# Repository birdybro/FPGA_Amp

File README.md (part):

# FPGA Amp

FPGA Amp is a physically informed vacuum-tube audio simulator. The immediate
target is a moving-magnet cartridge feeding the two triodes of a 12AX7 through
the passive RIAA network published by Kevin Kennedy in 1998. It is modeled as a
coupled electrical circuit—not as an EQ block followed by a waveshaper.

```text
AT-VM95E R/L source -> 47.5 kΩ || 150 pF -> 12AX7 #1
 -> 47 nF / 210 kΩ / 33.2 kΩ / 10 nF / 3.3 nF passive RIAA
 -> 12AX7 #2 -> 470 nF -> 2.21 MΩ line load
```

The project keeps three categories separate:

- **Reference:** the frozen 1998 circuit, including its measured low-frequency
  RIAA departure.
- **Approximation:** tube-model, integration, LUT, fixed-point, solver, and RTL
  errors measured against the immediately upstream reference.
- **Enhancement:** future subsonic filtering, tube variation, noise, and other
  modern/creative controls, all explicitly opt-in.

## Current measured milestone

The mono reference and complete 768 kHz circuit solver are operating:

- ngspice DC: stage 1 is 180.0 V / 0.992 mA and stage 2 is 192.8 V /
  1.072 mA at a 300 V supply.
- SPICE circuit gain is 41.087 dB at 1 kHz. Relative RIAA error is
  -0.919 to +0.000 dB from 20 Hz to 20 kHz; this is a property of the frozen
  historical network, not digitally corrected.
- The 768 kHz backward-Euler nonlinear nodal model differs from the ngspice
  5 mV-peak, 1 kHz result by -53.10 dB normalized residual and 0.0018 dB RMS
  gain, with no failed solves.
- A four-frequency SPICE transient sweep exposes backward-Euler's audio-band
  phase cost: at 100 Hz it is +0.00131 dB / +0.0244°, while at 20 kHz it is
  -0.0646 dB / +4.72°. Raising backward-Euler to 3.072 MHz still leaves 1.24°
  at 20 kHz. An explicit 768 kHz trapezoidal candidate improves 10/20 kHz
  floating error to at most 0.00846 dB / 0.0582°.
- A separately labeled 384 kHz/8× trapezoidal architecture candidate measures
  at most 0.06653 dB / 0.02234° against the same 10/20 kHz SPICE captures. At
  20 kHz, its complete-circuit selected 4/8/12/16 kHz products remain within
  0.52 dB of 768 kHz for 5 mV, 20 mV, and steady 0.5 V inputs, while a hot
  static-tube stress is 11.33 dB worse but still -118.65 dBc. Distinct
  fixed-point assets now match 1,024 all-bank chord, 1,024 KCL, and 512
  persistent full-solver RTL vectors exactly at 384 kHz with zero solver
  diagnostics. The 127-clock core
  leaves 129 of 256 clocks free at 98.304 MHz. Its Q17.1 chord inverse requires
  signed 19-bit coefficients rather than the 768 kHz core's 18 bits; controlled
  Yosys synthesis measures 13,713 LC / 183 DSP / 10 RAMB18 equivalents versus
  13,158 LC / 174 DSP / 10 RAMB18 equivalents at 768 kHz. The complete
  candidate stream now matches 64 external outputs across 512 nonlinear
  updates exactly, with zero converter, solver, or deadline diagnostics.
  After serializing each decimator center tap and replacing both resamplers'
  reset-cleared shift histories with reset-masked circular distributed memory,
  controlled full-stream synthesis measures 15,716 LC / 8,547 FF / 207 DSP /
  10 RAMB18 equivalents at 384 kHz versus 16,062 / 9,033 / 206 / 10 for 768 kHz.
  Reference mode remains 16×/768 kHz. A 772,608-update paired fixed-stream
  campaign finds
  8× recovery only 0.1875 ms later, with -84.71 dB aligned waveform and
  -81.02 dB audio-band residuals. Known-delay, windowed-sinc alignment measures
  the synthetic pop at -35.92 dB overall, 2.623 mV peak error, and -53.33 dB
  in-band. A layer decomposition measures the identity converters at -67.49 dB
  in-band, floating Newton at -55.71 dB, and fixed at -53.33 dB; same-rate
  fixed/float nulls remain about -59 dB. This supersedes an invalid earlier
  linear-interpolation result. Direct RTL capture matches the corresponding
  fixed models for all 24,576 pop/recovery outputs and 294,912 nonlinear
  updates at both rates with zero diagnostics. A matched, unfitted absolute
  pop-response comparison against ngspice measures -61.47 dB residual at the
  48 kHz output boundary for 384 kHz and -61.00 dB for 768 kHz; maximum errors
  are 0.539 and 0.546 mV, respectively, with zero failed floating solves. This
  experiment therefore does not support keeping 16× on transient-accuracy
  grounds. The earlier shifting-history three-pin harness packs on XC7A100T at
  63,902 LUTX / 14,737 FFX / 4,071 CARRY4 / 207 DSP, but heap placement does
  not legalize. That baseline legally places on XC7A200T with
  nextpnr's static placer at only 34.40 MHz versus 98.304 MHz. The experimental
  backend's `DEFAULT` grade is not qualified -1 signoff, but the 2.86× miss is
  decisive enough to skip routing. An explicit 49.152 MHz fabric schedule then
  halves every enable interval while preserving the same 384 kHz arithmetic:
  its 127-clock solver fits exactly within the 128-clock internal period, and
  the complete 64-output/512-update regression remains bit-exact with zero
  diagnostics. Baseline static A200T placement improves to 38.34 MHz versus
  49.152 MHz. Circular decimator history then cuts the packed design to 58,363
  LUTX / 10,562 FFX / 4,099 CARRY4 / 207 DSP and makes heap placement legal for
  the first time, but its 22.79 MHz estimate still fails timing. Static
  placement initially reaches 38.38 MHz. Circular interpolation then reduces
  the pack to 56,041 LUTX / 8,589 FFX / 4,116 CARRY4 / 207 DSP and improves
  static placement to 41.27 MHz. The completed legal route reaches 48.482 MHz,
  only 1.38% below 49.152 MHz. Its 20.626 ns critical path starts at solver
  state selection, crosses voltage selection and plate-pin conversion, and
  ends in the factorized-tube input mapping. A separately named exact
  123-clock parallel/pipelined profile instead grows to 242 DSPs and places at
  only 39.62 MHz, so it is rejected. A route-guided tube-pin prefetch plus
  diagnostic-only KCL maximum pipeline also preserves all 64 outputs / 512
  updates and the 127-clock latency. After removing an invalid-only dead
  maximum load it routes legally at 47.07 MHz, but its 21.24 ns chord-preview
  path is slower than the baseline and is likewise not promoted. The route
  remains diagnostic rather than timing closure or a bitstream claim. A
  zero-latency late-selector candidate instead converts current and corrected
  stage-one tube pins independently and selects only the two 32-bit pin buses.
  It remains bit-exact at 127 clocks, synthesizes to 15,645 LC / 8,589 FF /
  207 DSP / 10 RAMB18 equivalents, and routes legally at 48.700 MHz in seed 1.
  That is the best measured route but still misses 49.152 MHz by 0.92%; seed 2
  reaches only 45.051 MHz. Combining it with the register-heavy four-boundary
  maximum sideband was stopped after a pathological first routing iteration
  and is not promoted. A lower-state serial maximum instead scans the nine
  stable residual rows during terminal chord work. It matches 2,048 KCL
  vectors and the complete stream exactly, reduces the pack to 54,699 LUTX /
  8,657 FFX / 4,044 CARRY4 / 207 DSP, and routes legally in 14 iterations, but
  reaches only 47.567 MHz through the now-exposed chord-to-tube path.
  Registering the six raw tube nodes on the exact one-cycle-early chord preview
  removes that path without adding a solver clock: the same complete stream is
  bit-exact at 127 clocks, Yosys measures 15,220 LC / 8,855 FF / 207 DSP /
  10 RAMB18 equivalents, and a legal seed-1 A200T route reaches 61.072 MHz
  against 49.152 MHz. The 16.37 ns critical path is now terminal-current/state
  arithmetic, with 6.44 ns logic and 9.94 ns routing. This closes the target
  under nextpnr's experimental `DEFAULT` grade. Seed 2 independently routes at
  51.080 MHz with 0.77 ns positive estimated slack and a different 19.58 ns
  registered-node-to-tube critical path. Neither result is qualified -1
  signoff or physical validation. The selected seed-1 FASM now also passes a
  wholly open Project-X-Ray bitstream stage: 20,230 frame records become a
  reproducible 9,730,907-byte `.bit`, and `bitread -C` validates 24,060
  configuration frames / 2,432,650 words. Two conversions have identical
  SHA-256 `98a53adf...2b9dcb`; the script fixes only header timestamp metadata
  and records that hardware remains unprogrammed/unvalidated. The 8×
  architecture remains an explicit candidate and reference mode remains 16×.
  The selected 8× profile now also runs through the actual calibrated fabric
  adapter, asynchronous I²S bridge, register bank, and SPI transport. Exact
  regressions cover 64 adapter frames, 64 serial inputs / 44 observable DAC
  frames, control transitions, and 15 SPI frames. Yosys measures 15,699 LC /
  9,085 FF for the adapter and 16,614 LC / 11,586 FF for the full SPI/I²S top;
  both use 217 DSPs / 10 RAMB18 equivalents with zero structural problems.
  The Nexys Video clock leaf now cascades two checked XC7 MMCMs from its real
  100 MHz oscillator to exact 12.288 MHz codec MCLK and 49.152 MHz fabric
  clocks. Its clock-only open route and CRC-readable bitstream pass. A tested
  /16 divider now produces 3.072 MHz BCLK with owning-domain reset release;
  a bus-level-tested open-drain I2C writer and 27-register ADAU1761 startup
  sequence pass exact-byte and fail-stop NACK simulation. The codec layer is
  warning-free in XC7 synthesis at 88 estimated logic cells / 94 flip-flops /
  no DSP or BRAM. The codec remains subordinate to FPGA-provided BCLK/LRCLK,
  and line unmute occurs last. The actual Nexys Video wrapper now composes that
  clock/reset/bootstrap path with one shared codec LRCLK, the 384 kHz
  timing-closed phono profile, SPI control, open-drain I2C, and fail-closed DAC
  data. A mutation-tested contract checks all 18 LOC/IOSTANDARD pairs, active-
  low reset, internal 3.072 MHz BCLK constraint, model rate, and startup mute;
  a separate guard regression proves that serial DAC data stays zero and the
  I2S bridge/FIFO serial ports stay reset through two BCLK synchronizer edges
  after configuration. This prevents undefined ADC frames during the 10 ms
  bootstrap from pre-filling the receive FIFO. Complete synthesis reports
  16,688 estimated logic cells / 11,687 flip-flops / 217 DSPs / ten RAMB18
  equivalents and zero structural problems. Programming, physical ACKs,
  analog audio, and clock measurements remain open. The full open A200T route
  converges legally in 20 iterations and estimates 54.663 MHz against the
  49.152 MHz fabric constraint and 123.457 MHz against 3.072 MHz BCLK. The
  pinned Project-X-Ray stage twice emits the same CRC-readable 9,730,825-byte
  bitstream at SHA-256 `5f196e52...b09dbb8`. This closes the experimental open
  implementation gate only; the `DEFAULT` timing grade is not qualified -1
  signoff and the image has not been programmed. A non-programming hardware
  preflight now rechecks that exact artifact's part, length, SHA-256, and saved
  `bitread -C` evidence before asking openFPGALoader to detect the official
  `nexysVideo` board profile. The current host has neither openFPGALoader nor a
  Nexys Video USB device, so physical bring-up is explicitly blocked rather
  than inferred from the image.
- A 100 ms floating overload comparison finds the trapezoidal candidate finite
  and convergent through 1.5 V peak / 26.4 µA stage-two grid current. At 20 mV,
  its 10% / 1% / 1 mV recovery agrees with backward Euler within 2.6 µs. Both
  retain the modeled long recovery above 0.5 V; trapezoidal does not conceal or
  correct that reference behavior.
- The bit-accurate trapezoidal candidate uses the wide Q28/Q32 node contract,
  Q30 previous capacitor voltage, and explicit signed Q4.44 previous capacitor
  current. Across six 5 mV points from 20 Hz through 20 kHz it stays within
  0.000131 dB / 0.000784° of floating trapezoidal, with zero convergence,
  saturation, range, or correction-fallback events. Its RTL is bit-exact at the
  same 116-clock schedule, including the banked large-signal captures below.
  It remains an optional numerical candidate rather than a silent reference
  change.
- In the 5 ms burst gate, fixed trapezoidal stays diagnostic-clean through
  0.5 V peak and retains the same severe-overload boundary as backward Euler:
  1.0/1.5 V cause 1,107/1,690 residual failures and 1.5 V causes 4,048 tube-
  domain clips. Stored capacitor current reaches 203.34 uA with no arithmetic
  saturation. The doubled 470 nF companion coefficient requires signed 48-bit
  Q0.47, one bit wider than the current backward-Euler RTL KCL contract.
- The 128 × 256 Q0.31 tube LUT has 0.139 µA mean and 9.33 µA worst absolute
  error in a 100,000-point full-range probe.
- The complete bit-accurate three-pass chord candidate is -57.87 dB normalized
  residual from analytical/full-Newton float on the initial multitone; isolated
  state/chord error is -70.33 dB relative to the same circuit using the tube LUT.
- A settled 1 kHz sweep exposes a narrower low-level limitation: at 5 mV peak,
  fixed THD is 0.0733% versus 0.0191% analytical. Doubling either LUT axis does
  not fix the existing 2-D implementation.
- A new factorized Koren candidate replaces that current surface with three
  value/slope 1-D tables and cubic Hermite interpolation. Its bit-accurate Python
  model measures 50.6 nA worst plate-current error in 100,000 points and 0.0188%
  THD at 5 mV versus 0.0191% analytical. Its 1,024-point grid-current branch
  measures 12.55 nA worst / 2.82 nA active-region RMS error; total raw storage
  is 262,144 bits (14.22 raw RAMB18 equivalents). Standalone RTL is exact across
  4,110 vectors at the existing eight-clock latency; structural synthesis
  reports 1,496 logic cells, 35 DSP48E1s, and 8 RAMB18E1 + 1 RAMB36E1. Solver and
  complete-stream modes are also
  bit-exact at the unchanged 126-clock solver schedule.
- A separately named value-only factorized candidate keeps the physical Koren
  factorization and eight-clock interface while using 1,024/8,192/4,096 linear
  tables. Its dense fixed probe measures 47.49 nA worst plate-current error;
  tube, wide-solver, and complete 127-clock terminal-solver RTL are bit-exact.
  The isolated tube routes at 113.24 MHz with 27 DSPs. Full solver synthesis
  uses 166 DSPs and 13 RAMB18E1 + 5 RAMB36E1; routing is still in progress, so
  this remains an FPGA approximation candidate rather than reference mode.
- The SystemVerilog tube lookup accepts physical Q-format voltages, is
  bit-exact for 4,096 randomized vectors, and has eight-clock latency.
- The nine-node chord corrector is bit-exact for 1,024 randomized/boundary
  vectors, including 18 saturation cases, with ten-clock latency; XC7 synthesis
  uses 9 DSP48E1 blocks and no block RAM.
- A device-neutral depth-8 dual-clock FIFO now crosses full audio words with
  binary local/Gray synchronized pointers, two-flop CDC synchronizers, registered
  reads, sticky overflow/underflow, and conservative local-domain occupancy plus
  high-water diagnostics. Unrelated 100/71.4 MHz test clocks preserve a 128-word
  wrap sequence after directed full/empty faults; directed fill reaches exactly
  depth eight and both estimates return to zero after drain. Generic XC7 synthesis
  uses 127 logic cells / 331 flip-flops / no DSP or RAM; Yosys intentionally
  expands this small 8×32 memory to registers. Embedded formal invariants exist,
  and a depth-four formal instance now passes 13 properties for all arbitrary
  clock/control interleavings over 32 global steps. A separate trace reaches
  full plus both fault stickies. This is bounded safety evidence, not unbounded
  induction or a physical metastability claim.
- Separate I²S receive/transmit blocks now implement signed 24-bit stereo in
  32-BCLK slots with the mandatory one-clock I²S delay. A warning-free 16-frame
  loopback covers positive/negative endpoints, independent 32-period slot/delay
  monitoring, injected LRCLK framing failure, and transmit underflow/clear.
  Warning-free XC7 synthesis measures 35 LC / 105 rising-edge flops for receive
  and 97 LC / 137 falling-edge flops for transmit, with no DSP or RAM.
- A bidirectional I²S asynchronous bridge now composes those protocol blocks
  with independent depth-8 stereo-frame FIFOs. A warning-free test sends 20
  exact frames from BCLK to an unrelated fabric clock and back while applying
  fabric receive backpressure; all six bridge diagnostics remain clean apart
  from deliberate DAC startup starvation, which clears in its owning domain.
  Directed multi-frame receive backpressure records 3/3-frame receive and
  4/4-frame transmit high-water marks without loss. Flattened XC7
  synthesis reports 571 LC / 1,547 FF / no DSP or RAM. The small
  8×64 memories are explicitly register-expanded.
- A Gray-counter audio-clock monitor now measures BCLK over 32,768 fabric
  clocks, accepts 1,024 ± 1 edges, and requires three consecutive windows for
  lock. Warning-free directed RTL acquires at the exact ratio, observes 11
  rather than 10 edges after a deliberate speed change, drops lock/latches the
  error, reacquires, clears, detects a stopped clock as zero edges, and revokes
  live state on BCLK reset. Sixteen properties hold over 32-step arbitrary-clock
  traces in a reduced instance, and a witness locks before retaining a bad-rate
  error. The pin top measures exactly 1,024 edges in four windows. Standalone
  synthesis is 68 LC / 125 FF / no DSP or RAM. This detects gross rate error;
  FIFO drift remains the longer-term mismatch diagnostic and neither mechanism
  performs rate matching.
  The register-controlled wrapper now treats missing lock or retained rate
  error as an explicitly modern immediate-mute condition. A shortened-window
  integration test proves startup qualification, stopped-BCLK clamp, recovery
  that remains latched, coherent fault snapshot, and host clear before release;
  model scheduling continues silently so the receive FIFO is not filled.
- A reusable 16-bit held-bus CDC snapshot now uses a four-phase handshake, two
  data synchronizer stages, and a final settling clock. Three warning-free
  captures survive unrelated clocks and a destination reset during a request;
  nine properties also hold for every 40-step arbitrary-clock formal
  interleaving after shared startup reset, with a nonzero complete-transfer
  witness. Generic synthesis is 5 LC / 75 FF with no warnings. The register
  bank waits for this capture before advancing its snapshot sequence and packs
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
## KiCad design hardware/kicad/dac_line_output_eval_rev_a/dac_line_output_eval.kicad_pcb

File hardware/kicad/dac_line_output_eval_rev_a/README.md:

# PCM5242 DAC / protected line-output Rev-A EVT board

This directory contains a routed four-layer KiCad 10 evaluation board for the
stereo FPGA-to-line-output path. It is a concrete bench prototype, not a
production fabrication release and not evidence of measured audio performance.
Open `dac_line_output_eval.kicad_pro` in KiCad 10. KiCad does not live-reload
files changed by the generator, so close/reopen the board after regeneration.

```text
FPGA 24-bit I2S + 24.576 MHz SCK
  -> PCM5242 in external-clock slave / I2C mode
  +-> 499 ohm/leg + 1 nF differential reconstruction -> fail-open relays -> balanced harness
  +-> 499 ohm + 2.2 nF shunt reconstruction -> fail-open relay -> isolated-RCA harness
```

The board is 112 x 72 mm with F.Cu / continuous L2 GND / L3 POWER_SIG /
B.Cu. Digital/control entry, DAC and charge pump, reconstruction networks,
relays, and panel harnesses are physically partitioned. The harness connectors
are EVT choices; production XLR/RCA mechanics belong to the enclosure design.

## Fixed electrical contract

- DAC: PCM5242RHBR, 48 kHz slave, 24-bit I2S in 32-BCK channel slots.
- Clocks: 24.576 MHz external SCK (`512 fS`), 3.072 MHz BCK (`64 fS`), and
  48 kHz LRCK. External SCK is used instead of making the DAC PLL the reference.
- Control: I2C mode with `MODE1=0`, `MODE2=1`, `ADR1=0`, and `ADR2=0`.
  Reference firmware must hold XSMT low while configuring and reading back a
  unity path; optional miniDSP/creative processing is disabled in reference
  mode.
- Supplies: separate external 3.7 V analog and digital feeds post-regulated by
  two TPS7A2033 devices, plus a separate 5 V relay feed. The power board owns
  sequencing and the single reviewed chassis/signal-ground bond.
- Balanced output: the official EVM-style 499 ohm per-leg and 1 nF
  differential network. Into 20 kilohm differential, calculated full scale is
  4.00038 V RMS at DC and 3.97214 V RMS at 20 kHz.
- RCA output: the data-sheet-style 499 ohm / 2.2 nF single-ended network. Into
  10 kilohm, calculated full scale is 2.00019 V RMS at DC and 1.98314 V RMS at
  20 kHz.
- Output switching: three Omron G6K-2F-Y 5 V relays use only normally-open
  contacts, so loss of power opens every signal output.

Two SN74LVC1G08 gates provide independent fail-low interlocks:

```text
LINE_RELAY_EN_SAFE = LINE_RELAY_EN_CTL AND HARD_MUTE_N
DAC_XSMT_SAFE      = DAC_SOFT_UNMUTE_CTL AND HARD_MUTE_N
```

Each input is pulled low. The external supervisor can therefore force both
PCM5242 soft mute and physical relay mute even if the controller is stuck high,
reset, absent, or unpowered. The intended unmute order is configure/read back
the DAC while XSMT is low, energize output relays, then raise XSMT. Mute reverses
that order after allowing the DAC ramp to finish.

`design.py` is the auditable source for exact clock, loading, output-level, and
reconstruction-response calculations. Its committed result is
`design_calculations.json`.

## Reproduction and verification

From the repository root:

```sh
make kicad-dac-line-check
make kicad-dac-line-render
```

To regenerate and route from source, set `FREEROUTING_JAR` to Freerouting 2.2.4
or a verified compatible release:

```sh
make kicad-dac-line-route FREEROUTING_JAR=/path/to/freerouting.jar
make kicad-dac-line-check
```

The route script rotates the PCM5242 so its clock pins face the digital side and
its four analog outputs face the reconstruction networks. Freerouting completes
the dense routing; a deterministic reviewed back-edge trace finishes J2.4 I2C
SDA without passing through the header's other even-numbered pads.

The committed board passes KiCad ERC and DRC with zero violations and zero
unconnected items. `verify.py` also locks the PCM5242 and interlock pad maps,
mode straps, normally-open relay contacts, filter values, DNP chassis options,
calculation consistency, board stack/outline, and minimum routing geometry.

The matching open RTL now includes the 20-write configuration bootstrap,
24-operation page-aware readback verifier, and periodic clock/error/short/power
monitor. The integrated controller requires a 48-transaction success path
before `unmute_permitted` and revokes it on a later fault. A separate
`dac_line_output_sequencer` maps that permission to the actual board pins:
`LINE_RELAY_EN_CTL` rises first, `DAC_SOFT_UNMUTE_CTL` follows after a default
5 ms, and orderly mute reverses the order. Emergency mute drops both registered
permissions on the next fabric edge; `HARD_MUTE_N` remains the independent
asynchronous hardware veto. All bus/sequence tests and Yosys structural checks
pass, but no populated-board timing or audio behavior is claimed.

## Release gates

Do not order this as a production board until all of the following are closed:

- PCM5242 control is integrated onto the selected FPGA pins and every physical
  mute transition is verified with the external supervisor able to dominate a
  stuck controller;
- loaded THD+N, dynamic range, frequency response, channel balance, crosstalk,
  output impedance, DC, and clipping are measured on populated hardware;
- power-up, shutdown, brownout, missing-clock, hot-plug, and harness-unplug
  behavior are measured without an audible or damaging transient;
- enclosure-qualified XLR/RCA connectors, pin-1/chassis treatment, isolated
  RCA mounting, and keyed harnesses are selected;
- the provisional PESD5V0X1BCL output clamps pass leakage/capacitance/audio and
  IEC ESD/EFT/RF-immunity qualification; and
- a fabricator stackup, DFM, return-current, thermal, assembly, and sourcing
  review is complete.

## Primary component sources

- [TI PCM5242 data sheet](https://www.ti.com/lit/ds/symlink/pcm5242.pdf)
- [TI PCM5242EVM user guide](https://www.ti.com/lit/ug/slau592a/slau592a.pdf)
- [TI TPS7A20 data sheet](https://www.ti.com/lit/ds/symlink/tps7a20.pdf)
- [TI SN74LVC1G08 data sheet](https://www.ti.com/lit/ds/symlink/sn74lvc1g08.pdf)
- [Omron G6K relay family](https://components.omron.com/sg-en/products/relays/G6K)

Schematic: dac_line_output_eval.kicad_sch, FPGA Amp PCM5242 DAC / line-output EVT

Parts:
C1: 10nF_X7R; C_0603_1608Metric
C2: 100nF_X7R_LDOO; C_0402_1005Metric
C3: 2.2uF_X7R_FLY; C_0603_1608Metric
C4: 2.2uF_X7R_VNEG; C_0603_1608Metric
C5: 100nF_X7R_AVDD; C_0402_1005Metric
C6: 10uF_X5R_AVDD; C_0805_2012Metric
C7: 100nF_X7R_CPVDD; C_0402_1005Metric
C8: 2.2uF_X7R_CPVDD; C_0603_1608Metric
C9: 100nF_X7R_DVDD; C_0402_1005Metric
C10: 10uF_X5R_DVDD; C_0805_2012Metric
C11, C12: 100nF_X7R; C_0402_1005Metric
C20, C21: 1nF_C0G_DIFF; C_0603_1608Metric
C22, C23: 2.2nF_C0G_SE; C_0603_1608Metric
C30, C33: 1uF_X7R_LDO_IN; C_0805_2012Metric
C31, C34: 2.2uF_X7R_LDO_OUT; C_0805_2012Metric
C32: 10uF_X5R_ANALOG_BULK; C_0805_2012Metric
C35: 10uF_X5R_DIGITAL_BULK; C_0805_2012Metric
C36: 10uF_X5R_RELAY_BULK; C_0805_2012Metric
C50: DNP_4.7nF_CHASSIS; C_1206_3216Metric
D1, D2, D3: 1N4148W_FLYBACK; D_SOD-123
D4, D5, D6, D7, D8, D9: PESD5V0X1BCL_EVT; D_SOD-882
J1: DAC_AUDIO; PinHeader_2x05_P2.54mm_Vertical
J2: DAC_CONTROL; PinHeader_2x05_P2.54mm_Vertical
J3: POWER_INPUT; PinHeader_2x04_P2.54mm_Vertical
J4: BALANCED_PANEL_HARNESS_EVT; JST_XH_B8B-XH-A_1x08_P2.50mm_Vertical
J5: RCA_PANEL_HARNESS_EVT; JST_XH_B3B-XH-A_1x03_P2.50mm_Vertical
K1: G6K-2F-Y-5V_FAIL_OPEN_1; Relay_DPDT_Omron_G6K-2F-Y
K2: G6K-2F-Y-5V_FAIL_OPEN_2; Relay_DPDT_Omron_G6K-2F-Y
K3: G6K-2F-Y-5V_FAIL_OPEN_3; Relay_DPDT_Omron_G6K-2F-Y
Q1, Q2, Q3: MMBT3904; SOT-23
R1, R2, R3, R4: 0R_LINK; R_0402_1005Metric
R5: 1k; R_0603_1608Metric
R6, R12, R13, R14: 100k_FAIL_MUTE; R_0603_1608Metric
R7, R8: 4.7k; R_0603_1608Metric
R9, R10: 0R_LINK; R_0603_1608Metric
R11: 10k; R_0603_1608Metric
R20, R21, R22, R23, R24, R25: 499R_0.1%; R_0805_2012Metric
R31, R32, R33: 2.2k; R_0603_1608Metric
R34, R35, R36: 100k; R_0603_1608Metric
R40: 1R_ANALOG_ISOLATION; R_0805_2012Metric
R50: DNP_0R_CHASSIS_BOND; R_1206_3216Metric
TP1: +3V3A; TestPoint_Pad_D1.0mm
TP2: +3V3D; TestPoint_Pad_D1.0mm
TP3: DAC_XSMT_PIN; TestPoint_Pad_D1.0mm
TP4: LINE_RELAY_EN_SAFE; TestPoint_Pad_D1.0mm
TP5: L_RCA_OUT; TestPoint_Pad_D1.0mm
TP6: R_RCA_OUT; TestPoint_Pad_D1.0mm
TP7: CHASSIS; TestPoint_Pad_D1.0mm
TP8: GND; TestPoint_Pad_D1.0mm
U1: PCM5242RHBR; Texas_RHB0032E_VQFN-32-1EP_5x5mm_P0.5mm_EP3.45x3.45mm_Therm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
U2: TPS7A2033PDBVR_ANALOG; SOT-23-5
U3: TPS7A2033PDBVR_DIGITAL; SOT-23-5
U4: SN74LVC1G08DBVR_RELAY_INTERLOCK; SOT-23-5
U5: SN74LVC1G08DBVR_XSMT_INTERLOCK; SOT-23-5

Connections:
+3V3A: C5.1 (+3V3A), C6.1 (+3V3A), C7.1 (+3V3A), C8.1 (+3V3A), C32.1 (+3V3A), R40.2 (+3V3A), TP1.1, U1.5 (+3V3A), U1.14 (+3V3A)
+3V3A_RAW: C31.1 (+3V3A_RAW), R40.1 (+3V3A_RAW), U2.5 (+3V3A_RAW)
+3V3D: C9.1 (+3V3D), C10.1 (+3V3D), C11.1 (+3V3D), C12.1 (+3V3D), C34.1 (+3V3D), C35.1 (+3V3D), J1.9 (+3V3D), J2.1 (+3V3D), R7.1 (+3V3D), R8.1 (+3V3D), TP2.1, U1.4 (+3V3D), U1.24 (+3V3D), U3.5 (+3V3D), U4.5 (+3V3D), U5.5 (+3V3D)
+3V7A_IN: C30.1 (+3V7A_IN), J3.1 (+3V7A_IN), U2.1 (+3V7A_IN), U2.3 (+3V7A_IN)
+3V7D_IN: C33.1 (+3V7D_IN), J3.3 (+3V7D_IN), U3.1 (+3V7D_IN), U3.3 (+3V7D_IN)
+5V_RELAY: C36.1 (+5V_RELAY), D1.1 (+5V_RELAY), D2.1 (+5V_RELAY), D3.1 (+5V_RELAY), J3.5 (+5V_RELAY), K1.1 (+5V_RELAY), K2.1 (+5V_RELAY), K3.1 (+5V_RELAY)
CHASSIS: C50.1 (CHASSIS), D4.1 (CHASSIS), D5.1 (CHASSIS), D6.1 (CHASSIS), D7.1 (CHASSIS), D8.1 (CHASSIS), D9.1 (CHASSIS), J3.7 (CHASSIS), J4.3 (CHASSIS), J4.7 (CHASSIS), R50.1 (CHASSIS), TP7.1
CP_FLY_N: C3.2 (CP_FLY_N), U1.8 (CP_FLY_N)
CP_FLY_P: C3.1 (CP_FLY_P), U1.6 (CP_FLY_P)
DAC_BCK: R2.2 (DAC_BCK), U1.27 (DAC_BCK)
DAC_BCK_IN: J1.3 (DAC_BCK_IN), R2.1 (DAC_BCK_IN)
DAC_DIN: R4.2 (DAC_DIN), U1.28 (DAC_DIN)
DAC_DIN_IN: J1.7 (DAC_DIN_IN), R4.1 (DAC_DIN_IN)
DAC_LDOO: C2.1 (DAC_LDOO), U1.2 (DAC_LDOO)
DAC_LN: R21.1 (DAC_LN), U1.11 (DAC_LN)
DAC_LP: R20.1 (DAC_LP), R24.1 (DAC_LP), U1.10 (DAC_LP)
DAC_LRCK: R3.2 (DAC_LRCK), U1.31 (DAC_LRCK)
DAC_LRCK_IN: J1.5 (DAC_LRCK_IN), R3.1 (DAC_LRCK_IN)
DAC_RN: R23.1 (DAC_RN), U1.12 (DAC_RN)
DAC_RP: R22.1 (DAC_RP), R25.1 (DAC_RP), U1.13 (DAC_RP)
DAC_SCK: R1.2 (DAC_SCK), U1.26 (DAC_SCK)
DAC_SCK_IN: J1.1 (DAC_SCK_IN), R1.1 (DAC_SCK_IN)
DAC_SOFT_UNMUTE_CTL: J2.5 (DAC_SOFT_UNMUTE_CTL), R14.1 (DAC_SOFT_UNMUTE_CTL), U5.1 (DAC_SOFT_UNMUTE_CTL)
DAC_VNEG: C4.1 (DAC_VNEG), U1.9 (DAC_VNEG)
DAC_XSMT_PIN: C1.1 (DAC_XSMT_PIN), R5.2 (DAC_XSMT_PIN), R6.1 (DAC_XSMT_PIN), TP3.1, U1.1 (DAC_XSMT_PIN)
DAC_XSMT_SAFE: R5.1 (DAC_XSMT_SAFE), U5.4 (DAC_XSMT_SAFE)
GND: C1.2 (GND), C2.2 (GND), C4.2 (GND), C5.2 (GND), C6.2 (GND), C7.2 (GND), C8.2 (GND), C9.2 (GND), C10.2 (GND), C11.2 (GND), C12.2 (GND), C22.2 (GND), C23.2 (GND), C30.2 (GND), C31.2 (GND), C32.2 (GND), C33.2 (GND), C34.2 (GND), C35.2 (GND), C36.2 (GND), C50.2 (GND), J1.2 (GND), J1.4 (GND), J1.6 (GND), J1.8 (GND), J1.10 (GND), J2.2 (GND), J2.9 (GND), J2.10 (GND), J3.2 (GND), J3.4 (GND), J3.6 (GND), J3.8 (GND), J4.4 (GND), J4.8 (GND), J5.2 (GND), Q1.2 (GND), Q2.2 (GND), Q3.2 (GND), R6.2 (GND), R11.2 (GND), R12.2 (GND), R13.2 (GND), R14.2 (GND), R34.2 (GND), R35.2 (GND), R36.2 (GND), R50.2 (GND), TP8.1, U1.3 (GND), U1.7 (GND), U1.15 (GND), U1.22 (GND), U1.23 (GND), U1.32 (GND), U1.33 (GND), U2.2 (GND), U3.2 (GND), U4.3 (GND), U5.3 (GND)
HARD_MUTE_N: J2.8 (HARD_MUTE_N), R13.1 (HARD_MUTE_N), U4.2 (HARD_MUTE_N), U5.2 (HARD_MUTE_N)
I2C_SCL: R7.2 (I2C_SCL), R9.2 (I2C_SCL), U1.18 (I2C_SCL)
I2C_SCL_IN: J2.3 (I2C_SCL_IN), R9.1 (I2C_SCL_IN)
I2C_SDA: R8.2 (I2C_SDA), R10.2 (I2C_SDA), U1.17 (I2C_SDA)
I2C_SDA_IN: J2.4 (I2C_SDA_IN), R10.1 (I2C_SDA_IN)
K1_BASE: Q1.1 (K1_BASE), R31.2 (K1_BASE), R34.1 (K1_BASE)
K1_COIL_LOW: D1.2 (K1_COIL_LOW), K1.8 (K1_COIL_LOW), Q1.3 (K1_COIL_LOW)
K2_BASE: Q2.1 (K2_BASE), R32.2 (K2_BASE), R35.1 (K2_BASE)
K2_COIL_LOW: D2.2 (K2_COIL_LOW), K2.8 (K2_COIL_LOW), Q2.3 (K2_COIL_LOW)
K3_BASE: Q3.1 (K3_BASE), R33.2 (K3_BASE), R36.1 (K3_BASE)
K3_COIL_LOW: D3.2 (K3_COIL_LOW), K3.8 (K3_COIL_LOW), Q3.3 (K3_COIL_LOW)
LINE_RELAY_EN_CTL: J2.6 (LINE_RELAY_EN_CTL), R12.1 (LINE_RELAY_EN_CTL), U4.1 (LINE_RELAY_EN_CTL)
LINE_RELAY_EN_SAFE: R31.1 (LINE_RELAY_EN_SAFE), R32.1 (LINE_RELAY_EN_SAFE), R33.1 (LINE_RELAY_EN_SAFE), TP4.1, U4.4 (LINE_RELAY_EN_SAFE)
L_BAL_N_FILT: C20.2 (L_BAL_N_FILT), K1.6 (L_BAL_N_FILT), R21.2 (L_BAL_N_FILT)
L_BAL_N_OUT: D5.2 (L_BAL_N_OUT), J4.2 (L_BAL_N_OUT), K1.5 (L_BAL_N_OUT)
L_BAL_P_FILT: C20.1 (L_BAL_P_FILT), K1.3 (L_BAL_P_FILT), R20.2 (L_BAL_P_FILT)
L_BAL_P_OUT: D4.2 (L_BAL_P_OUT), J4.1 (L_BAL_P_OUT), K1.4 (L_BAL_P_OUT)
L_RCA_FILT: C22.1 (L_RCA_FILT), K3.3 (L_RCA_FILT), R24.2 (L_RCA_FILT)
L_RCA_OUT: D8.2 (L_RCA_OUT), J5.1 (L_RCA_OUT), K3.4 (L_RCA_OUT), TP5.1
OB_PRESENT_N: J2.7 (OB_PRESENT_N), R11.1 (OB_PRESENT_N)
R_BAL_N_FILT: C21.2 (R_BAL_N_FILT), K2.6 (R_BAL_N_FILT), R23.2 (R_BAL_N_FILT)
R_BAL_N_OUT: D7.2 (R_BAL_N_OUT), J4.6 (R_BAL_N_OUT), K2.5 (R_BAL_N_OUT)
R_BAL_P_FILT: C21.1 (R_BAL_P_FILT), K2.3 (R_BAL_P_FILT), R22.2 (R_BAL_P_FILT)
R_BAL_P_OUT: D6.2 (R_BAL_P_OUT), J4.5 (R_BAL_P_OUT), K2.4 (R_BAL_P_OUT)
R_RCA_FILT: C23.1 (R_RCA_FILT), K3.6 (R_RCA_FILT), R25.2 (R_RCA_FILT)
R_RCA_OUT: D9.2 (R_RCA_OUT), J5.3 (R_RCA_OUT), K3.5 (R_RCA_OUT), TP6.1

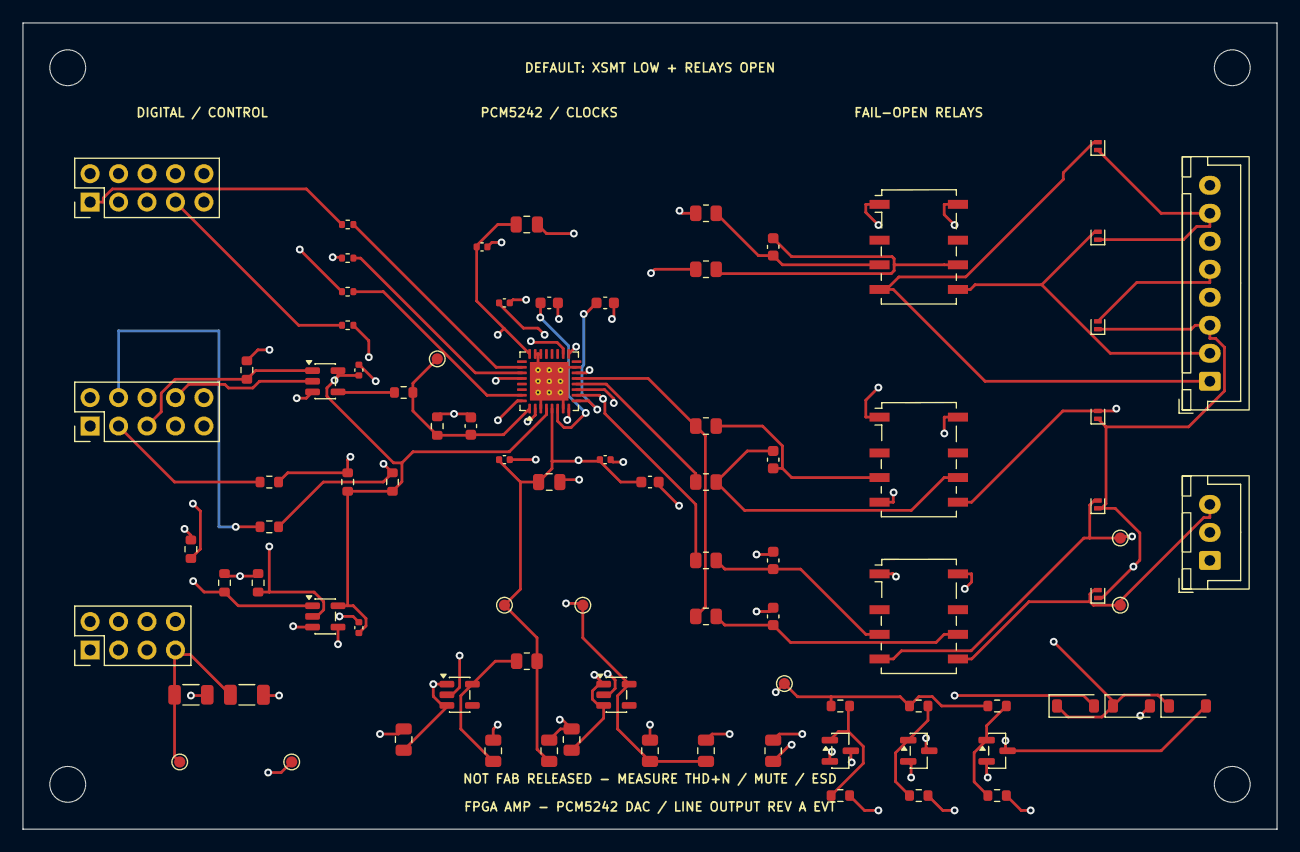
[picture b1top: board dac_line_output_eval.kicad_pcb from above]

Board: 4 copper layers, 112.0 x 72.0 mm, 89 parts (0 on the bottom side), 53 nets.

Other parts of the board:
H1, H2, H3, H4: M3_CHASSIS_STANDOFF; MountingHole_3.2mm_M3

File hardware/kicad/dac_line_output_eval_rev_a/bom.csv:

Reference,Value,Footprint,Description
J1,DAC_AUDIO,Connector_PinHeader_2.54mm:PinHeader_2x05_P2.54mm_Vertical,24.576MHz SCK; 3.072MHz BCK; 48kHz LRCK; 24-bit I2S from digital board
J2,DAC_CONTROL,Connector_PinHeader_2.54mm:PinHeader_2x05_P2.54mm_Vertical,Low-speed control; DAC and relay paths fail muted
J3,POWER_INPUT,Connector_PinHeader_2.54mm:PinHeader_2x04_P2.54mm_Vertical,Separate analog; digital; relay; chassis; and return feeds from power board
J4,BALANCED_PANEL_HARNESS_EVT,Connector_JST:JST_XH_B8B-XH-A_1x08_P2.50mm_Vertical,EVT harness to enclosure XLRs; XLR pin 1 bonds to chassis at connector
J5,RCA_PANEL_HARNESS_EVT,Connector_JST:JST_XH_B3B-XH-A_1x03_P2.50mm_Vertical,EVT harness to isolated RCA output jacks
U1,PCM5242RHBR,Package_DFN_QFN:Texas_RHB0032E_VQFN-32-1EP_5x5mm_P0.5mm_EP3.45x3.45mm_ThermalVias,Stereo DirectPath DAC; I2C mode; slave clocks; external SCK; VREF output mode
U2,TPS7A2033PDBVR_ANALOG,Package_TO_SOT_SMD:SOT-23-5,Low-noise analog/charge-pump 3.3V post-regulator
U3,TPS7A2033PDBVR_DIGITAL,Package_TO_SOT_SMD:SOT-23-5,Low-noise digital 3.3V post-regulator
U4,SN74LVC1G08DBVR_RELAY_INTERLOCK,Package_TO_SOT_SMD:SOT-23-5,Hardware AND: controller and independent supervisor must both release line relays
U5,SN74LVC1G08DBVR_XSMT_INTERLOCK,Package_TO_SOT_SMD:SOT-23-5,Hardware AND: controller and independent supervisor must both release DAC XSMT
R1,0R_LINK,Resistor_SMD:R_0402_1005Metric,Receiver-side link; source damping belongs on digital board
R2,0R_LINK,Resistor_SMD:R_0402_1005Metric,Receiver-side link; source damping belongs on digital board
R3,0R_LINK,Resistor_SMD:R_0402_1005Metric,Receiver-side link; source damping belongs on digital board
R4,0R_LINK,Resistor_SMD:R_0402_1005Metric,Receiver-side link; source damping belongs on digital board
R5,1k,Resistor_SMD:R_0603_1608Metric,
R6,100k_FAIL_MUTE,Resistor_SMD:R_0603_1608Metric,
C1,10nF_X7R,Capacitor_SMD:C_0603_1608Metric,
R7,4.7k,Resistor_SMD:R_0603_1608Metric,
R8,4.7k,Resistor_SMD:R_0603_1608Metric,
R9,0R_LINK,Resistor_SMD:R_0603_1608Metric,
R10,0R_LINK,Resistor_SMD:R_0603_1608Metric,
R11,10k,Resistor_SMD:R_0603_1608Metric,
R12,100k_FAIL_MUTE,Resistor_SMD:R_0603_1608Metric,
R13,100k_FAIL_MUTE,Resistor_SMD:R_0603_1608Metric,Independent supervisor release defaults low if disconnected
R14,100k_FAIL_MUTE,Resistor_SMD:R_0603_1608Metric,
C11,100nF_X7R,Capacitor_SMD:C_0402_1005Metric,U4 local bypass
C12,100nF_X7R,Capacitor_SMD:C_0402_1005Metric,U5 local bypass
C2,100nF_X7R_LDOO,Capacitor_SMD:C_0402_1005Metric,
C3,2.2uF_X7R_FLY,Capacitor_SMD:C_0603_1608Metric,
C4,2.2uF_X7R_VNEG,Capacitor_SMD:C_0603_1608Metric,
C5,100nF_X7R_AVDD,Capacitor_SMD:C_0402_1005Metric,
C6,10uF_X5R_AVDD,Capacitor_SMD:C_0805_2012Metric,
C7,100nF_X7R_CPVDD,Capacitor_SMD:C_0402_1005Metric,
C8,2.2uF_X7R_CPVDD,Capacitor_SMD:C_0603_1608Metric,
C9,100nF_X7R_DVDD,Capacitor_SMD:C_0402_1005Metric,
C10,10uF_X5R_DVDD,Capacitor_SMD:C_0805_2012Metric,
R20,499R_0.1%,Resistor_SMD:R_0805_2012Metric,
R21,499R_0.1%,Resistor_SMD:R_0805_2012Metric,
R22,499R_0.1%,Resistor_SMD:R_0805_2012Metric,
R23,499R_0.1%,Resistor_SMD:R_0805_2012Metric,
R24,499R_0.1%,Resistor_SMD:R_0805_2012Metric,
R25,499R_0.1%,Resistor_SMD:R_0805_2012Metric,
C20,1nF_C0G_DIFF,Capacitor_SMD:C_0603_1608Metric,
C21,1nF_C0G_DIFF,Capacitor_SMD:C_0603_1608Metric,
C22,2.2nF_C0G_SE,Capacitor_SMD:C_0603_1608Metric,
C23,2.2nF_C0G_SE,Capacitor_SMD:C_0603_1608Metric,
K1,G6K-2F-Y-5V_FAIL_OPEN_1,Relay_SMD:Relay_DPDT_Omron_G6K-2F-Y,Left balanced normally-open hard mute
Q1,MMBT3904,Package_TO_SOT_SMD:SOT-23,Independent low-side relay driver
R31,2.2k,Resistor_SMD:R_0603_1608Metric,
R34,100k,Resistor_SMD:R_0603_1608Metric,
D1,1N4148W_FLYBACK,Diode_SMD:D_SOD-123,
K2,G6K-2F-Y-5V_FAIL_OPEN_2,Relay_SMD:Relay_DPDT_Omron_G6K-2F-Y,Right balanced normally-open hard mute
Q2,MMBT3904,Package_TO_SOT_SMD:SOT-23,Independent low-side relay driver
R32,2.2k,Resistor_SMD:R_0603_1608Metric,
R35,100k,Resistor_SMD:R_0603_1608Metric,
D2,1N4148W_FLYBACK,Diode_SMD:D_SOD-123,
K3,G6K-2F-Y-5V_FAIL_OPEN_3,Relay_SMD:Relay_DPDT_Omron_G6K-2F-Y,Stereo RCA normally-open hard mute
Q3,MMBT3904,Package_TO_SOT_SMD:SOT-23,Independent low-side relay driver
R33,2.2k,Resistor_SMD:R_0603_1608Metric,
R36,100k,Resistor_SMD:R_0603_1608Metric,
D3,1N4148W_FLYBACK,Diode_SMD:D_SOD-123,
D4,PESD5V0X1BCL_EVT,Diode_SMD:D_SOD-882,EVT bidirectional line-output ESD candidate; qualify to IEC test plan
D5,PESD5V0X1BCL_EVT,Diode_SMD:D_SOD-882,EVT bidirectional line-output ESD candidate; qualify to IEC test plan
D6,PESD5V0X1BCL_EVT,Diode_SMD:D_SOD-882,EVT bidirectional line-output ESD candidate; qualify to IEC test plan
D7,PESD5V0X1BCL_EVT,Diode_SMD:D_SOD-882,EVT bidirectional line-output ESD candidate; qualify to IEC test plan
D8,PESD5V0X1BCL_EVT,Diode_SMD:D_SOD-882,EVT bidirectional line-output ESD candidate; qualify to IEC test plan
D9,PESD5V0X1BCL_EVT,Diode_SMD:D_SOD-882,EVT bidirectional line-output ESD candidate; qualify to IEC test plan
R40,1R_ANALOG_ISOLATION,Resistor_SMD:R_0805_2012Metric,
C30,1uF_X7R_LDO_IN,Capacitor_SMD:C_0805_2012Metric,
C31,2.2uF_X7R_LDO_OUT,Capacitor_SMD:C_0805_2012Metric,
C32,10uF_X5R_ANALOG_BULK,Capacitor_SMD:C_0805_2012Metric,
C33,1uF_X7R_LDO_IN,Capacitor_SMD:C_0805_2012Metric,
C34,2.2uF_X7R_LDO_OUT,Capacitor_SMD:C_0805_2012Metric,
C35,10uF_X5R_DIGITAL_BULK,Capacitor_SMD:C_0805_2012Metric,
C36,10uF_X5R_RELAY_BULK,Capacitor_SMD:C_0805_2012Metric,
R50,DNP_0R_CHASSIS_BOND,Resistor_SMD:R_1206_3216Metric,DNP; populate only from complete chassis grounding review
C50,DNP_4.7nF_CHASSIS,Capacitor_SMD:C_1206_3216Metric,DNP; safety/EMC population requires rated part and review
TP1,+3V3A,TestPoint:TestPoint_Pad_D1.0mm,Local EVT pogo point
TP2,+3V3D,TestPoint:TestPoint_Pad_D1.0mm,Local EVT pogo point
TP3,DAC_XSMT_PIN,TestPoint:TestPoint_Pad_D1.0mm,Local EVT pogo point
TP4,LINE_RELAY_EN_SAFE,TestPoint:TestPoint_Pad_D1.0mm,Local EVT pogo point
TP5,L_RCA_OUT,TestPoint:TestPoint_Pad_D1.0mm,Local EVT pogo point
TP6,R_RCA_OUT,TestPoint:TestPoint_Pad_D1.0mm,Local EVT pogo point
TP7,CHASSIS,TestPoint:TestPoint_Pad_D1.0mm,Local EVT pogo point
TP8,GND,TestPoint:TestPoint_Pad_D1.0mm,Local EVT pogo point

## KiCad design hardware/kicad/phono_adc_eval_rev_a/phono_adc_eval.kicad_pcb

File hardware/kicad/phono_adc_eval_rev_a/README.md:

# Shielded MM phono / PCM4202 ADC Rev-A EVT board

This directory contains a routed four-layer KiCad 10 evaluation board for the
flat-gain Architecture A input path. It is a concrete bench prototype, not a
production fabrication release and not evidence of measured performance.

```text
isolated panel RCA harness -> 100 ohm RF limiter -> 47.5 kilohm load
  -> selectable 0/47/100/147 pF C0G load -> OPA1656 flat gain
  -> OPA1632 fully differential driver/filter -> PCM4202 stereo ADC
  -> 24-bit I2S to the FPGA board
```

The board is 130 x 90 mm with F.Cu / continuous L2 GND / L3 POWER_SIG /
B.Cu. Cartridge entry, relay loading, flat gain, differential drivers, ADC,
local post-regulation, and digital headers are physically partitioned. The RCA
and turntable-ground connectors are EVT harness/terminal choices; production
parts remain enclosure decisions.

## Fixed electrical contract

- ADC: PCM4202DBR, 48 kHz single-rate master, 24-bit I2S.
- SCKI: 24.576 MHz from the digital board (`512 fS`).
- ADC outputs: 6.144 MHz BCK (`128 fS`), 48 kHz LRCK, serial data, and L/R
  clip indicators. `pcm4202_i2s_capture` now receives this exact 64-BCK
  half-frame format and crosses it into fabric in RTL simulation; pin timing
  and populated-board operation remain unverified.
- PCM4202 straps: `S/M=0`, `FMT1:FMT0=01`, `FS2:FS0=001`, `HPFD=1`.
  `HPFD=1` disables the converter high-pass filter so reference mode retains
  the external circuit's low-frequency behavior.
- Analog rails: TPS7A39 local +12.0/-11.9 V from external +/-15.5 V;
  TPS7A2050 +5 V from +5.7 V; TPS7A2033 +3.3 V from +3.7 V. Relay +5 V is
  supplied separately.
- Input termination: 47.5 kilohm, 0.1%, per channel. Installed capacitance is
  switchable in 47 pF and 100 pF increments. Cable, connector, ESD, relay,
  amplifier, and PCB parasitics are additional and must be measured.
- ADC reset and all relay controls fail low. The signal path must be hardware
  muted before changing gain or capacitance.

The gain relay truth table is:

| `GAIN_BANK_CTL` | `GAIN_RANGE_CTL` | Selected gain | Meaning |
|---:|---:|---:|---|
| 0 | X | 26.064 dB | unpowered/reset default |
| 1 | 0 | 20.008 dB | high-headroom range |
| 1 | 1 | 32.002 dB | low-level range; 100 mV stress clips |

The capacitance relays act independently:

| `CAP_47PF_CTL` | `CAP_100PF_CTL` | Installed C0G increment |
|---:|---:|---:|
| 0 | 0 | 0 pF |
| 1 | 0 | 47 pF |
| 0 | 1 | 100 pF |
| 1 | 1 | 147 pF |

`design.py` is the auditable source for exact gain, headroom, clock, strap, and
rail calculations. Its committed result is `design_calculations.json`.

## Reproduction and verification

From the repository root:

```sh
make kicad-phono-adc-check
make kicad-phono-adc-render
```

To regenerate and autoroute from source, set `FREEROUTING_JAR` to Freerouting
2.2.4 or a verified compatible release and run:

```sh
make kicad-phono-adc-route FREEROUTING_JAR=/path/to/freerouting.jar
make kicad-phono-adc-check
```

The committed routed board passes KiCad ERC and DRC with zero violations and
zero unconnected items. `verify.py` additionally locks the critical IC and
relay pad maps, component population, ADC straps/clocks, layer structure,
outline, minimum routing geometry, and generated calculation consistency.

## Release gates

Do not order this as a production board until all of the following are closed:

- enclosure-qualified isolated RCA jacks and turntable ground-post mechanics;
- measured total input capacitance in every relay state;
- input-referred noise, hum, gain, overload recovery, channel separation, RF
  injection, and ESD tests on populated hardware;
- stackup/return-current and safety review with the intended enclosure/power
  board;
- 128-fS PCM4202 receive timing verified at physical FPGA pins (RTL simulation
  is complete); and
- muted relay switching and all power-up/down fault cases verified.

## Primary component sources

- [TI PCM4202 data sheet](https://www.ti.com/lit/ds/symlink/pcm4202.pdf)
- [TI OPA1656 data sheet](https://www.ti.com/lit/ds/symlink/opa1656.pdf)
- [TI OPA1632 data sheet](https://www.ti.com/lit/ds/symlink/opa1632.pdf)
- [TI TPS7A39 data sheet](https://www.ti.com/lit/ds/symlink/tps7a39.pdf)
- [TI TPS7A20 data sheet](https://www.ti.com/lit/ds/symlink/tps7a20.pdf)

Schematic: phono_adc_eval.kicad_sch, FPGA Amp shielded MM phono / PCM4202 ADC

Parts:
C1, C2: 47pF_C0G_1%; C_0603_1608Metric
C3, C4: 100pF_C0G_1%; C_0603_1608Metric
C5, C6: DNP_22pF_C0G_RF; C_0603_1608Metric
C20, C21, C30, C31: 1nF_C0G; C_0603_1608Metric
C22, C32: 2.7nF_C0G; C_0603_1608Metric
C23, C24, C33, C34: 100pF_C0G; C_0603_1608Metric
C40, C42, C46, C48: 33uF_LOW_ESR; C_Elec_4x5.8
C41, C43, C44, C45, C47, C49, C71, C72, C77, C78: 100nF_X7R; C_0603_1608Metric
C60, C61, C62: 10nF_X7R; C_0603_1608Metric
C63, C64, C65, C66, C79, C80: 10uF_25V_X7R; C_1206_3216Metric
C67, C68, C69, C70: 1uF_X7R; C_0603_1608Metric
C73, C74, C75, C76: 100nF_X7R; C_0402_1005Metric
C81: DNP_100nF_CHASSIS; C_1206_3216Metric
D1, D2: PESD5V0X1BCL_EVT; D_SOD-882
D3, D4, D5, D6: 1N4148W; D_SOD-123
J1: ISOLATED_PANEL_RCA_HARNESS; JST_XH_B3B-XH-A_1x03_P2.50mm_Vertical
J2: TURNTABLE_GROUND_POST; TerminalBlock_MetzConnect_360425_1x01_Horizontal_ScrewM4.0_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
J3: ADC_AUDIO; PinHeader_2x05_P2.54mm_Vertical
J4: POWER_INPUT; PinHeader_2x06_P2.54mm_Vertical
J5: ADC_CONTROL; PinHeader_2x05_P2.54mm_Vertical
K1: G6K-2F-Y-5V_GAIN_BANK; Relay_DPDT_Omron_G6K-2F-Y
K2: G6K-2F-Y-5V_GAIN_RANGE; Relay_DPDT_Omron_G6K-2F-Y
K3: G6K-2F-Y-5V_CAP47; Relay_DPDT_Omron_G6K-2F-Y
K4: G6K-2F-Y-5V_CAP100; Relay_DPDT_Omron_G6K-2F-Y
Q1, Q2, Q3, Q4: MMBT3904; SOT-23
R1, R2: 100R_0.1%; R_0805_2012Metric
R3, R4: 47.5k_0.1%_25ppm; R_0805_2012Metric
R5, R6: 19.1k_0.1%; R_0805_2012Metric
R7, R8: 1.00k_0.1%; R_0805_2012Metric
R9, R10: 2.12k_0.1%; R_0805_2012Metric
R11, R12: 492R_0.1%; R_0805_2012Metric
R20, R21, R22, R23, R30, R31, R32, R33: 316R_0.1%; R_0603_1608Metric
R24, R25, R34, R35: 40.2R_0.1%; R_0603_1608Metric
R40: 22R; R_0402_1005Metric
R41, R42, R43: 33R; R_0402_1005Metric
R44, R55, R56, R57, R58: 100k; R_0603_1608Metric
R45: 10k; R_0603_1608Metric
R51, R52, R53, R54: 2.2k; R_0603_1608Metric
R60: 90.9k_0.1%; R_0603_1608Metric
R61, R63: 10.0k_0.1%; R_0603_1608Metric
R62: 100k_0.1%; R_0603_1608Metric
R70: 0R_CHASSIS_BOND; R_1206_3216Metric
R71: DNP_10R_CHASSIS; R_1206_3216Metric
TP1: L_INPUT; TestPoint_Pad_D1.0mm
TP2: R_INPUT; TestPoint_Pad_D1.0mm
TP3: L_GAIN_OUT; TestPoint_Pad_D1.0mm
TP4: R_GAIN_OUT; TestPoint_Pad_D1.0mm
TP5: ADC_L_IN_P; TestPoint_Pad_D1.0mm
TP6: ADC_L_IN_N; TestPoint_Pad_D1.0mm
TP7: ADC_R_IN_P; TestPoint_Pad_D1.0mm
TP8: ADC_R_IN_N; TestPoint_Pad_D1.0mm
TP9: +12VA; TestPoint_Pad_D1.0mm
TP10: -12VA; TestPoint_Pad_D1.0mm
TP11: +5VA; TestPoint_Pad_D1.0mm
TP12: +3V3D; TestPoint_Pad_D1.0mm
TP13: SCKI_24M576; TestPoint_Pad_D1.0mm
TP14: ADC_BCK_OUT; TestPoint_Pad_D1.0mm
TP15: ADC_LRCK_OUT; TestPoint_Pad_D1.0mm
TP16: GND; TestPoint_Pad_D1.0mm
U1: TPS7A39DSCR; Texas_DSC0010J_ThermalVias
U2: TPS7A2050PDBVR; SOT-23-5
U3: TPS7A2033PDBVR; SOT-23-5
U4, U8: OPA1656IDR; SOIC-8_3.9x4.9mm_P1.27mm
U5, U6: OPA1632DR; SOIC-8_3.9x4.9mm_P1.27mm
U7: PCM4202DBR; SSOP-28_5.3x10.2mm_P0.65mm

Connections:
+3V3D: C48.1 (+3V3D), C49.1 (+3V3D), C70.1 (+3V3D), J5.1 (+3V3D), TP12.1, U3.5 (+3V3D), U7.6 (+3V3D), U7.9 (+3V3D), U7.12 (+3V3D), U7.14 (+3V3D)
+3V7_IN: C69.1 (+3V7_IN), J4.7 (+3V7_IN), U3.1 (+3V7_IN), U3.3 (+3V7_IN)
+5V7_IN: C67.1 (+5V7_IN), J4.5 (+5V7_IN), U2.1 (+5V7_IN), U2.3 (+5V7_IN)
+5VA: C46.1 (+5VA), C47.1 (+5VA), C68.1 (+5VA), TP11.1, U2.5 (+5VA), U7.22 (+5VA)
+5V_RELAY: D3.1 (+5V_RELAY), D4.1 (+5V_RELAY), D5.1 (+5V_RELAY), D6.1 (+5V_RELAY), J4.9 (+5V_RELAY), K1.1 (+5V_RELAY), K2.1 (+5V_RELAY), K3.1 (+5V_RELAY), K4.1 (+5V_RELAY)
+12VA: C61.1 (+12VA), C65.1 (+12VA), C71.1 (+12VA), C73.1 (+12VA), C75.1 (+12VA), C77.1 (+12VA), C79.1 (+12VA), R60.1 (+12VA), TP9.1, U1.10 (+12VA), U4.8 (+12VA), U5.3 (+12VA), U6.3 (+12VA), U8.8 (+12VA)
+15V5_IN: C63.1 (+15V5_IN), J4.1 (+15V5_IN), U1.1 (+15V5_IN), U1.2 (+15V5_IN)
-12VA: C62.1 (-12VA), C66.1 (-12VA), C72.1 (-12VA), C74.1 (-12VA), C76.1 (-12VA), C78.1 (-12VA), C80.1 (-12VA), R62.1 (-12VA), TP10.1, U1.6 (-12VA), U4.4 (-12VA), U5.6 (-12VA), U6.6 (-12VA), U8.4 (-12VA)
-15V5_IN: C64.1 (-15V5_IN), J4.3 (-15V5_IN), U1.5 (-15V5_IN)
AB_PRESENT_N: J5.8 (AB_PRESENT_N), R45.1 (AB_PRESENT_N)
ADC_BCK_OUT: J3.3 (ADC_BCK_OUT), R41.2 (ADC_BCK_OUT), TP14.1
ADC_BCK_SRC: R41.1 (ADC_BCK_SRC), U7.16 (ADC_BCK_SRC)
ADC_CLIP_L: J3.9 (ADC_CLIP_L), U7.21 (ADC_CLIP_L)
ADC_CLIP_R: J3.10 (ADC_CLIP_R), U7.20 (ADC_CLIP_R)
ADC_DATA_OUT: J3.7 (ADC_DATA_OUT), R43.2 (ADC_DATA_OUT)
ADC_DATA_SRC: R43.1 (ADC_DATA_SRC), U7.15 (ADC_DATA_SRC)
ADC_LRCK_OUT: J3.5 (ADC_LRCK_OUT), R42.2 (ADC_LRCK_OUT), TP15.1
ADC_LRCK_SRC: R42.1 (ADC_LRCK_SRC), U7.17 (ADC_LRCK_SRC)
ADC_L_IN_N: C22.2 (ADC_L_IN_N), C24.1 (ADC_L_IN_N), R25.2 (ADC_L_IN_N), TP6.1, U7.5 (ADC_L_IN_N)
ADC_L_IN_P: C22.1 (ADC_L_IN_P), C23.1 (ADC_L_IN_P), R24.2 (ADC_L_IN_P), TP5.1, U7.4 (ADC_L_IN_P)
ADC_RESET_N: J5.3 (ADC_RESET_N), R44.1 (ADC_RESET_N), U7.19 (ADC_RESET_N)
ADC_R_IN_N: C32.2 (ADC_R_IN_N), C34.1 (ADC_R_IN_N), R35.2 (ADC_R_IN_N), TP8.1, U7.24 (ADC_R_IN_N)
ADC_R_IN_P: C32.1 (ADC_R_IN_P), C33.1 (ADC_R_IN_P), R34.2 (ADC_R_IN_P), TP7.1, U7.25 (ADC_R_IN_P)
CAP_47PF_CTL: J5.6 (CAP_47PF_CTL), R53.1 (CAP_47PF_CTL)
CAP_100PF_CTL: J5.7 (CAP_100PF_CTL), R54.1 (CAP_100PF_CTL)
CHASSIS: C81.1 (CHASSIS), J2.1, R70.1 (CHASSIS), R71.1 (CHASSIS)
GAIN_BANK_CTL: J5.4 (GAIN_BANK_CTL), R51.1 (GAIN_BANK_CTL)
GAIN_RANGE_CTL: J5.5 (GAIN_RANGE_CTL), R52.1 (GAIN_RANGE_CTL)
GND: C1.2 (GND), C2.2 (GND), C3.2 (GND), C4.2 (GND), C5.2 (GND), C6.2 (GND), C23.2 (GND), C24.2 (GND), C33.2 (GND), C34.2 (GND), C40.2 (GND), C41.2 (GND), C42.2 (GND), C43.2 (GND), C44.2 (GND), C45.2 (GND), C46.2 (GND), C47.2 (GND), C48.2 (GND), C49.2 (GND), C60.2 (GND), C63.2 (GND), C64.2 (GND), C65.2 (GND), C66.2 (GND), C67.2 (GND), C68.2 (GND), C69.2 (GND), C70.2 (GND), C71.2 (GND), C72.2 (GND), C73.2 (GND), C74.2 (GND), C75.2 (GND), C76.2 (GND), C77.2 (GND), C78.2 (GND), C79.2 (GND), C80.2 (GND), C81.2 (GND), D1.1 (GND), D2.1 (GND), J1.2 (GND), J3.2 (GND), J3.4 (GND), J3.6 (GND), J3.8 (GND), J4.2 (GND), J4.4 (GND), J4.6 (GND), J4.8 (GND), J4.10 (GND), J4.12 (GND), J5.2 (GND), J5.9 (GND), J5.10 (GND), Q1.2 (GND), Q2.2 (GND), Q3.2 (GND), Q4.2 (GND), R3.2 (GND), R4.2 (GND), R7.2 (GND), R8.2 (GND), R9.2 (GND), R10.2 (GND), R11.2 (GND), R12.2 (GND), R21.1 (GND), R31.1 (GND), R44.2 (GND), R45.2 (GND), R55.2 (GND), R56.2 (GND), R57.2 (GND), R58.2 (GND), R61.2 (GND), R70.2 (GND), R71.2 (GND), TP16.1, U1.4 (GND), U1.11 (GND), U2.2 (GND), U3.2 (GND), U5.7 (GND), U6.7 (GND), U7.2 (GND), U7.7 (GND), U7.8 (GND), U7.10 (GND), U7.11 (GND), U7.13 (GND), U7.23 (GND), U7.27 (GND)
K1_BASE: Q1.1 (K1_BASE), R51.2 (K1_BASE), R55.1 (K1_BASE)
K1_COIL_LOW: D3.2 (K1_COIL_LOW), K1.8 (K1_COIL_LOW), Q1.3 (K1_COIL_LOW)
K2_BASE: Q2.1 (K2_BASE), R52.2 (K2_BASE), R56.1 (K2_BASE)
K2_COIL_LOW: D4.2 (K2_COIL_LOW), K2.8 (K2_COIL_LOW), Q2.3 (K2_COIL_LOW)
K3_BASE: Q3.1 (K3_BASE), R53.2 (K3_BASE), R57.1 (K3_BASE)
K3_COIL_LOW: D5.2 (K3_COIL_LOW), K3.8 (K3_COIL_LOW), Q3.3 (K3_COIL_LOW)
K4_BASE: Q4.1 (K4_BASE), R54.2 (K4_BASE), R58.1 (K4_BASE)
K4_COIL_LOW: D6.2 (K4_COIL_LOW), K4.8 (K4_COIL_LOW), Q4.3 (K4_COIL_LOW)
LDO_BUF: R63.2 (LDO_BUF), U1.8 (LDO_BUF)
LDO_FBN: C62.2 (LDO_FBN), R62.2 (LDO_FBN), R63.1 (LDO_FBN), U1.7 (LDO_FBN)
LDO_FBP: C61.2 (LDO_FBP), R60.2 (LDO_FBP), R61.1 (LDO_FBP), U1.9 (LDO_FBP)
LDO_NR: C60.1 (LDO_NR), U1.3 (LDO_NR)
L_CAP47: C1.1 (L_CAP47), K3.4 (L_CAP47)
L_CAP100: C3.1 (L_CAP100), K4.4 (L_CAP100)
L_DRV_IN_N: C21.2 (L_DRV_IN_N), R21.2 (L_DRV_IN_N), R23.2 (L_DRV_IN_N), U5.1 (L_DRV_IN_N)
L_DRV_IN_P: C20.2 (L_DRV_IN_P), R20.2 (L_DRV_IN_P), R22.2 (L_DRV_IN_P), U5.8 (L_DRV_IN_P)
L_DRV_OUT_N: C20.1 (L_DRV_OUT_N), R22.1 (L_DRV_OUT_N), R25.1 (L_DRV_OUT_N), U5.5 (L_DRV_OUT_N)
L_DRV_OUT_P: C21.1 (L_DRV_OUT_P), R23.1 (L_DRV_OUT_P), R24.1 (L_DRV_OUT_P), U5.4 (L_DRV_OUT_P)
L_GAIN20: K2.2 (L_GAIN20), R9.1 (L_GAIN20)
L_GAIN26: K1.2 (L_GAIN26), R7.1 (L_GAIN26)
L_GAIN32: K2.4 (L_GAIN32), R11.1 (L_GAIN32)
L_GAIN_ALT: K1.4 (L_GAIN_ALT), K2.3 (L_GAIN_ALT)
L_GAIN_N: K1.3 (L_GAIN_N), R5.2 (L_GAIN_N), U4.2 (L_GAIN_N)
L_GAIN_OUT: R5.1 (L_GAIN_OUT), R20.1 (L_GAIN_OUT), TP3.1, U4.1 (L_GAIN_OUT)
L_INPUT: C5.1 (L_INPUT), D1.2 (L_INPUT), K3.3 (L_INPUT), K4.3 (L_INPUT), R1.2 (L_INPUT), R3.1 (L_INPUT), TP1.1, U4.3 (L_INPUT)
L_INPUT_RAW: J1.1 (L_INPUT_RAW), R1.1 (L_INPUT_RAW)
L_VCOM_BUF: U5.2 (L_VCOM_BUF), U8.1 (L_VCOM_BUF), U8.2 (L_VCOM_BUF)
R_CAP47: C2.1 (R_CAP47), K3.5 (R_CAP47)
R_CAP100: C4.1 (R_CAP100), K4.5 (R_CAP100)
R_DRV_IN_N: C31.2 (R_DRV_IN_N), R31.2 (R_DRV_IN_N), R33.2 (R_DRV_IN_N), U6.1 (R_DRV_IN_N)
R_DRV_IN_P: C30.2 (R_DRV_IN_P), R30.2 (R_DRV_IN_P), R32.2 (R_DRV_IN_P), U6.8 (R_DRV_IN_P)
R_DRV_OUT_N: C30.1 (R_DRV_OUT_N), R32.1 (R_DRV_OUT_N), R35.1 (R_DRV_OUT_N), U6.5 (R_DRV_OUT_N)
R_DRV_OUT_P: C31.1 (R_DRV_OUT_P), R33.1 (R_DRV_OUT_P), R34.1 (R_DRV_OUT_P), U6.4 (R_DRV_OUT_P)
R_GAIN20: K2.7 (R_GAIN20), R10.1 (R_GAIN20)
R_GAIN26: K1.7 (R_GAIN26), R8.1 (R_GAIN26)
R_GAIN32: K2.5 (R_GAIN32), R12.1 (R_GAIN32)
R_GAIN_ALT: K1.5 (R_GAIN_ALT), K2.6 (R_GAIN_ALT)
R_GAIN_N: K1.6 (R_GAIN_N), R6.2 (R_GAIN_N), U4.6 (R_GAIN_N)
R_GAIN_OUT: R6.1 (R_GAIN_OUT), R30.1 (R_GAIN_OUT), TP4.1, U4.7 (R_GAIN_OUT)
R_INPUT: C6.1 (R_INPUT), D2.2 (R_INPUT), K3.6 (R_INPUT), K4.6 (R_INPUT), R2.2 (R_INPUT), R4.1 (R_INPUT), TP2.1, U4.5 (R_INPUT)
R_INPUT_RAW: J1.3 (R_INPUT_RAW), R2.1 (R_INPUT_RAW)
R_VCOM_BUF: U6.2 (R_VCOM_BUF), U8.6 (R_VCOM_BUF), U8.7 (R_VCOM_BUF)
SCKI_24M576: R40.2 (SCKI_24M576), TP13.1, U7.18 (SCKI_24M576)
SCKI_24M576_IN: J3.1 (SCKI_24M576_IN), R40.1 (SCKI_24M576_IN)
VCOM_L: C44.1 (VCOM_L), U7.3 (VCOM_L), U8.3 (VCOM_L)
VCOM_R: C45.1 (VCOM_R), U7.26 (VCOM_R), U8.5 (VCOM_R)
VREF_L: C40.1 (VREF_L), C41.1 (VREF_L), U7.1 (VREF_L)
VREF_R: C42.1 (VREF_R), C43.1 (VREF_R), U7.28 (VREF_R)

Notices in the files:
README.md:
GPL-3.0; see [`LICENSE`](LICENSE).
